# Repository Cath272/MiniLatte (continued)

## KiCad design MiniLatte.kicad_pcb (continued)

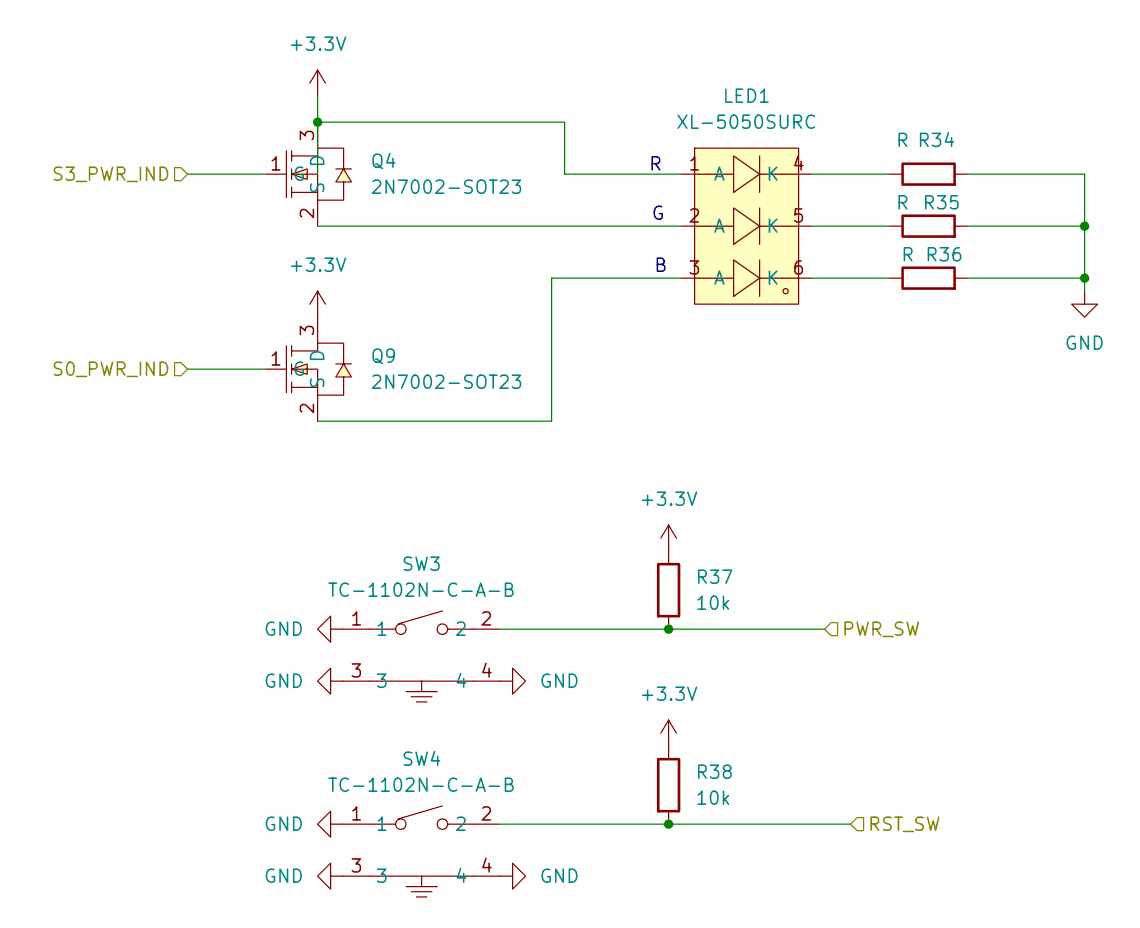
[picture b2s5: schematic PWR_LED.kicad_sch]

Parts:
LED1: XL-5050SURC; LED-ARRAY-SMD_6P-L5.0-W5.0-TL-RD-2; LCSC Part C2843864
Q4, Q9: 2N7002-SOT23; SOT-23_L2.9-W1.3-P1.90-LS2.4-BR; LCSC Part C332103
R34, R35, R36: R; R_0402_1005Metric
R37, R38: 10k; R_0402_1005Metric
SW3, SW4: TC-1102N-C-A-B; SW-TH_TC-1102N-C-A-B; LCSC Part C406152

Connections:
+3.3V: LED1.1 (A), Q4.3 (D), Q9.3 (D), R37.1, R38.1; also elsewhere on the board
/PWR_LED_SW/PWR_SW: R37.2, SW3.2; also elsewhere on the board
/PWR_LED_SW/RST_SW: R38.2, SW4.2; also elsewhere on the board
/PWR_LED_SW/S0_PWR_IND: Q9.1 (G); also elsewhere on the board
/PWR_LED_SW/S3_PWR_IND: Q4.1 (G); also elsewhere on the board
GND: R34.2, R35.2, R36.2, SW3.1, SW3.3, SW3.4, SW4.1, SW4.3, SW4.4; also elsewhere on the board
unnamed: LED1.4 (K), R34.1
unnamed: LED1.5 (K), R35.1
unnamed: LED1.6 (K), R36.1
unnamed: LED1.2 (A), Q4.2 (S)
unnamed: LED1.3 (A), Q9.2 (S)

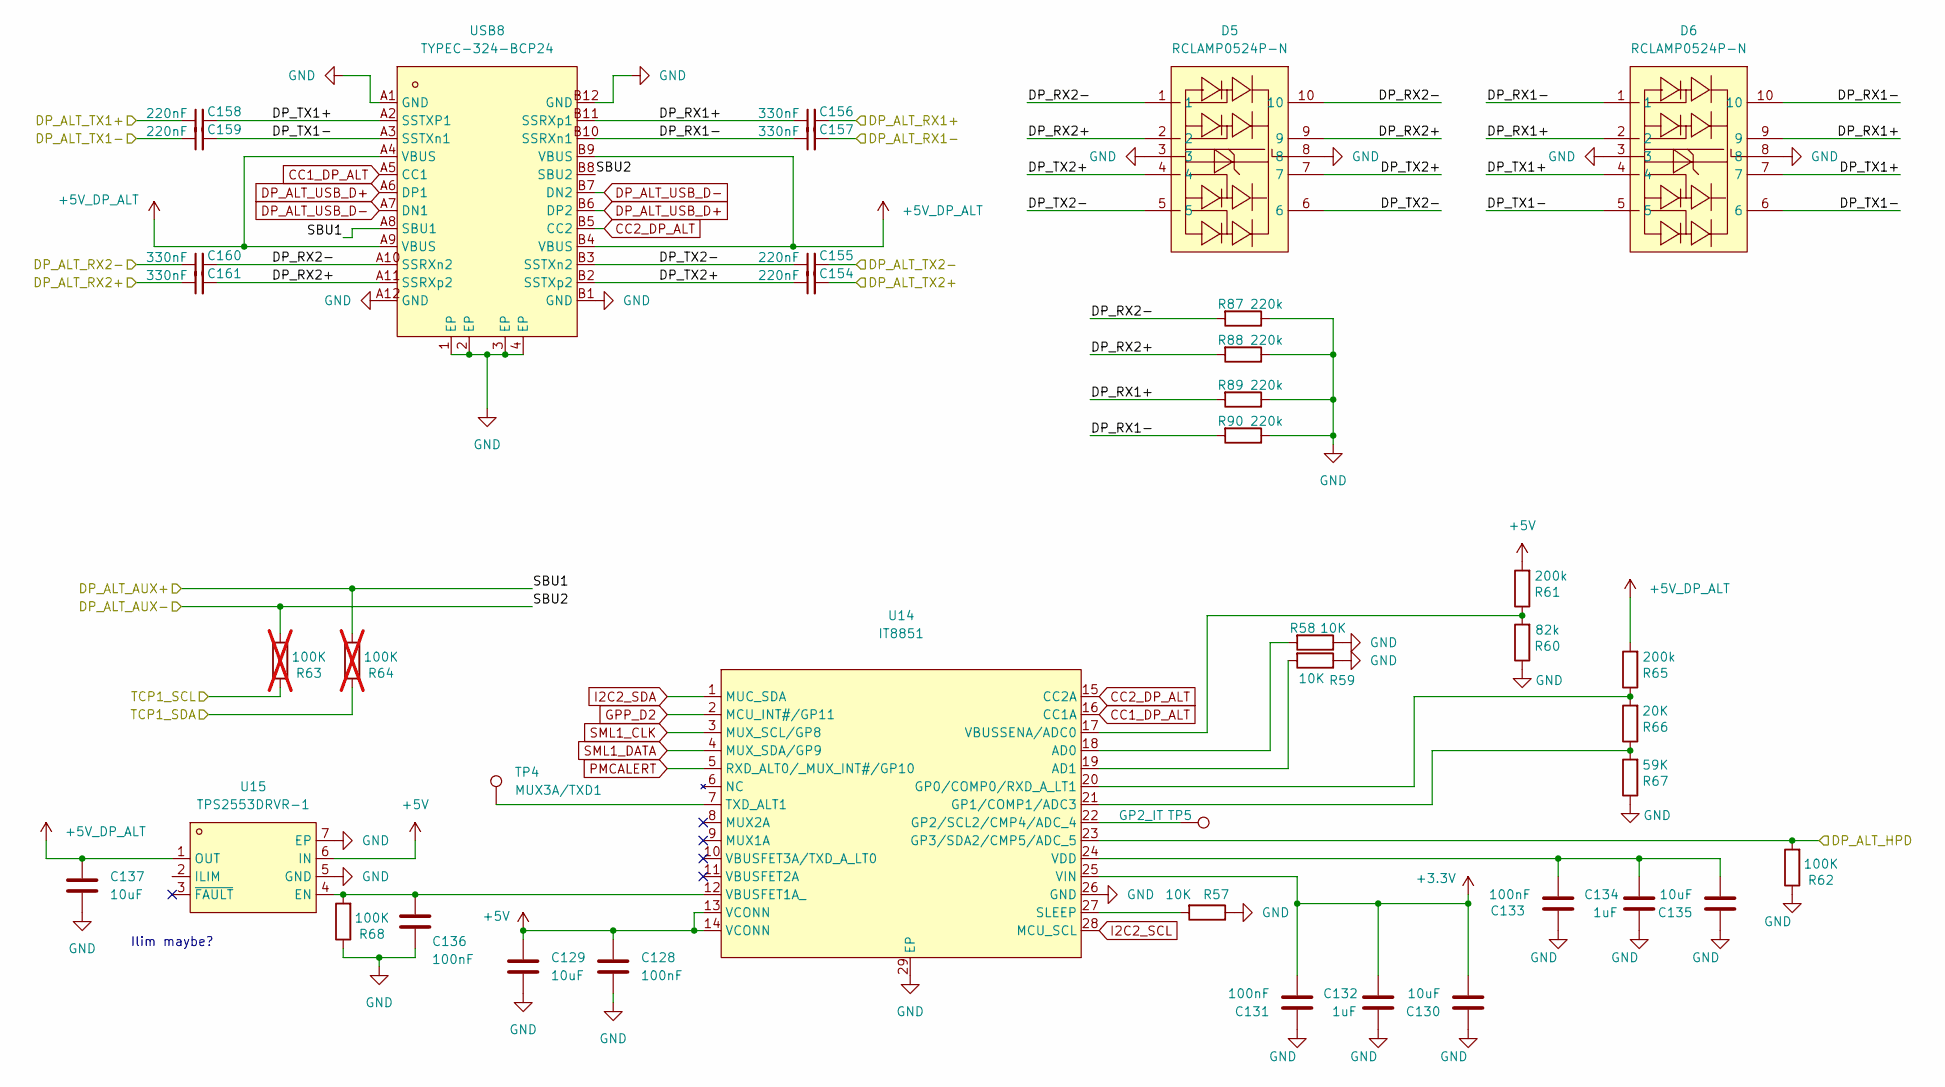
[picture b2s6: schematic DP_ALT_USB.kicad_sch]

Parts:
C128, C131, C133, C136: 100nF; C_0402_1005Metric
C129, C130, C135, C137: 10uF; C_0805_2012Metric
C132, C134: 1uF; C_0603_1608Metric
C154, C155, C158, C159: 220nF; C_0402_1005Metric
C156, C157, C160, C161: 330nF; C_0402_1005Metric
D5, D6: RCLAMP0524P-N; DFN-10L_L2.5-W1.0-P0.50-BL; LCSC Part C316044
R57, R58, R59: 10K; R_0402_1005Metric
R60: 82k; R_0402_1005Metric
R61, R65: 200k; R_0402_1005Metric
R62, R68: 100K; R_0402_1005Metric
R63, R64: 100K; R_0402_1005Metric; not fitted
R66: 20K; R_0402_1005Metric
R67: 59K; R_0402_1005Metric
R87, R88, R89, R90: 220k; R_0402_1005Metric
TP4: MUX3A/TXD1; TestPoint_Pad_D1.0mm
TP5: GP2_IT; TestPoint_Pad_D1.0mm
U14: IT8851; VQFN-28-1EP_4x4mm_P0.45mm_EP2.4x2.4mm
U15: TPS2553DRVR-1; WSON-6_L2.0-W2.0-P0.65-BL-EP; LCSC Part C411878
USB8: TYPEC-324-BCP24; USB-C-SMD_TYPEC-324-BCP24; LCSC Part C2835314

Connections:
+3.3V: C130.2, C131.2, C132.2, U14.25 (VIN); also elsewhere on the board
+5V: C128.1, C129.1, R61.2, U14.13 (VCONN), U14.14 (VCONN), U15.6 (IN); also elsewhere on the board
+5V_DP_ALT: C137.1, R65.2, U15.1 (OUT), USB8.A4 (VBUS), USB8.A9 (VBUS), USB8.B4 (VBUS), USB8.B9 (VBUS)
/DP_ALT_USB/DP_ALT_HPD: R62.2, U14.23 (GP3/SDA2/CMP5/ADC_5); also elsewhere on the board
/DP_ALT_USB/DP_ALT_RX1+: C156.2; also elsewhere on the board
/DP_ALT_USB/DP_ALT_RX1-: C157.2; also elsewhere on the board
/DP_ALT_USB/DP_ALT_RX2+: C161.1; also elsewhere on the board
/DP_ALT_USB/DP_ALT_RX2-: C160.1; also elsewhere on the board
/DP_ALT_USB/DP_ALT_TX1+: C158.1; also elsewhere on the board
/DP_ALT_USB/DP_ALT_TX1-: C159.1; also elsewhere on the board
/DP_ALT_USB/DP_ALT_TX2+: C154.2; also elsewhere on the board
/DP_ALT_USB/DP_ALT_TX2-: C155.2; also elsewhere on the board
/DP_ALT_USB/DP_RX1+: C156.1, D6.2, D6.9, R89.2, USB8.B11 (SSRXp1)
/DP_ALT_USB/DP_RX1-: C157.1, D6.1, D6.10, R90.2, USB8.B10 (SSRXn1)
/DP_ALT_USB/DP_RX2+: C161.2, D5.2, D5.9, R88.2, USB8.A11 (SSRXp2)
/DP_ALT_USB/DP_RX2-: C160.2, D5.1, D5.10, R87.2, USB8.A10 (SSRXn2)
/DP_ALT_USB/DP_TX1+: C158.2, D6.4, D6.7, USB8.A2 (SSTXP1)
/DP_ALT_USB/DP_TX1-: C159.2, D6.5, D6.6, USB8.A3 (SSTXn1)
/DP_ALT_USB/DP_TX2+: C154.1, D5.4, D5.7, USB8.B2 (SSTXp2)
/DP_ALT_USB/DP_TX2-: C155.1, D5.5, D5.6, USB8.B3 (SSTXn2)
/DP_ALT_USB/SBU1: R64.2, USB8.A8 (SBU1); also elsewhere on the board
/DP_ALT_USB/SBU2: R63.2, USB8.B8 (SBU2); also elsewhere on the board
/DP_ALT_USB/TCP1_SCL: R63.1; also elsewhere on the board
/DP_ALT_USB/TCP1_SDA: R64.1; also elsewhere on the board
CC1_DP_ALT: U14.16 (CC1A), USB8.A5 (CC1)
CC2_DP_ALT: U14.15 (CC2A), USB8.B5 (CC2)
DP_ALT_USB_D+: USB8.A6 (DP1), USB8.B6 (DP2); also elsewhere on the board
DP_ALT_USB_D-: USB8.A7 (DN1), USB8.B7 (DN2); also elsewhere on the board
GND: C128.2, C129.2, C130.1, C131.1, C132.1, C133.1, C134.1, C135.1, C136.2, C137.2, D5.3, D5.8, D6.3, D6.8, R57.1, R58.1, R59.1, R60.1, R62.1, R67.1, R68.1, R87.1, R88.1, R89.1, R90.1, U14.26 (GND), U14.29 (EP), U15.5 (GND), U15.7 (EP), USB8.1 (EP), USB8.2 (EP), USB8.3 (EP), USB8.4 (EP), USB8.A1 (GND), USB8.A12 (GND), USB8.B1 (GND), USB8.B12 (GND); also elsewhere on the board
GPP_D2: U14.2 (MCU_INT#/GP11); also elsewhere on the board
I2C2_SCL: U14.28 (MCU_SCL); also elsewhere on the board
I2C2_SDA: U14.1 (MUC_SDA); also elsewhere on the board
unnamed: R58.2, U14.18 (AD0)
unnamed: R59.2, U14.19 (AD1)
unnamed: R65.1, R66.2, U14.20 (GP0/COMP0/RXD_A_LT1)
unnamed: R66.1, R67.2, U14.21 (GP1/COMP1/ADC3)
unnamed: TP5.1, U14.22 (GP2/SCL2/CMP4/ADC_4)
unnamed: R57.2, U14.27 (SLEEP)
unnamed: TP4.1, U14.7 (TXD_ALT1)
unnamed: C136.1, R68.2, U14.12 (VBUSFET1A_), U15.4 (EN)
unnamed: R60.2, R61.1, U14.17 (VBUSSENA/ADC0)
unnamed: C133.2, C134.2, C135.2, U14.24 (VDD)
PMCALERT: U14.5 (RXD_ALT0/_MUX_INT#/GP10); also elsewhere on the board
SML1_CLK: U14.3 (MUX_SCL/GP8); also elsewhere on the board
SML1_DATA: U14.4 (MUX_SDA/GP9); also elsewhere on the board

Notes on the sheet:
Ilim maybe?

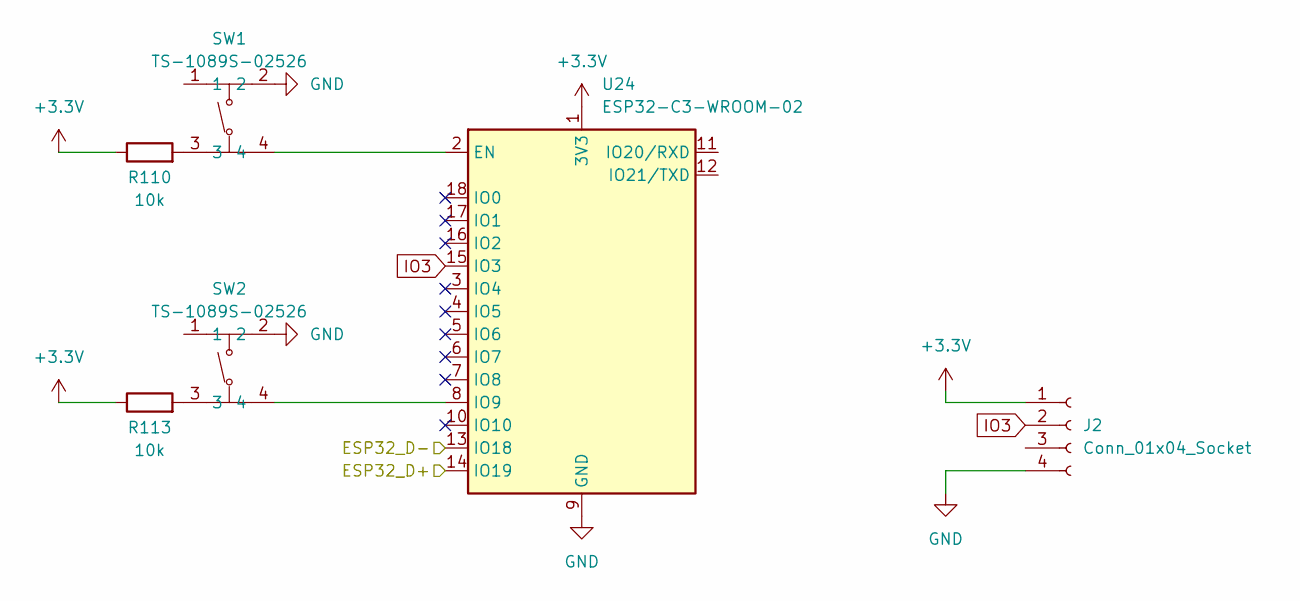
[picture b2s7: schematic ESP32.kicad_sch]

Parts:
J2: Conn_01x04_Socket; PinSocket_1x04_P2.54mm_Vertical
R110, R113: 10k; R_0402_1005Metric
SW1, SW2: TS-1089S-02526; SW-SMD_4P-L4.2-W3.3-P2.15-LS5.1; LCSC Part C455282
U24: ESP32-C3-WROOM-02

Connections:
+3.3V: J2.1, R110.1, R113.1, U24.1 (3V3); also elsewhere on the board
/ESP32/ESP32_D+: U24.14 (IO19); also elsewhere on the board
/ESP32/ESP32_D-: U24.13 (IO18); also elsewhere on the board
GND: J2.4, SW1.2, SW2.2, U24.9 (GND), U24.19 (GND); also elsewhere on the board
IO3: J2.2, U24.15 (IO3)
unnamed: R110.2, SW1.3
unnamed: R113.2, SW2.3
unnamed: SW1.4, U24.2 (EN)
unnamed: SW2.4, U24.8 (IO9)

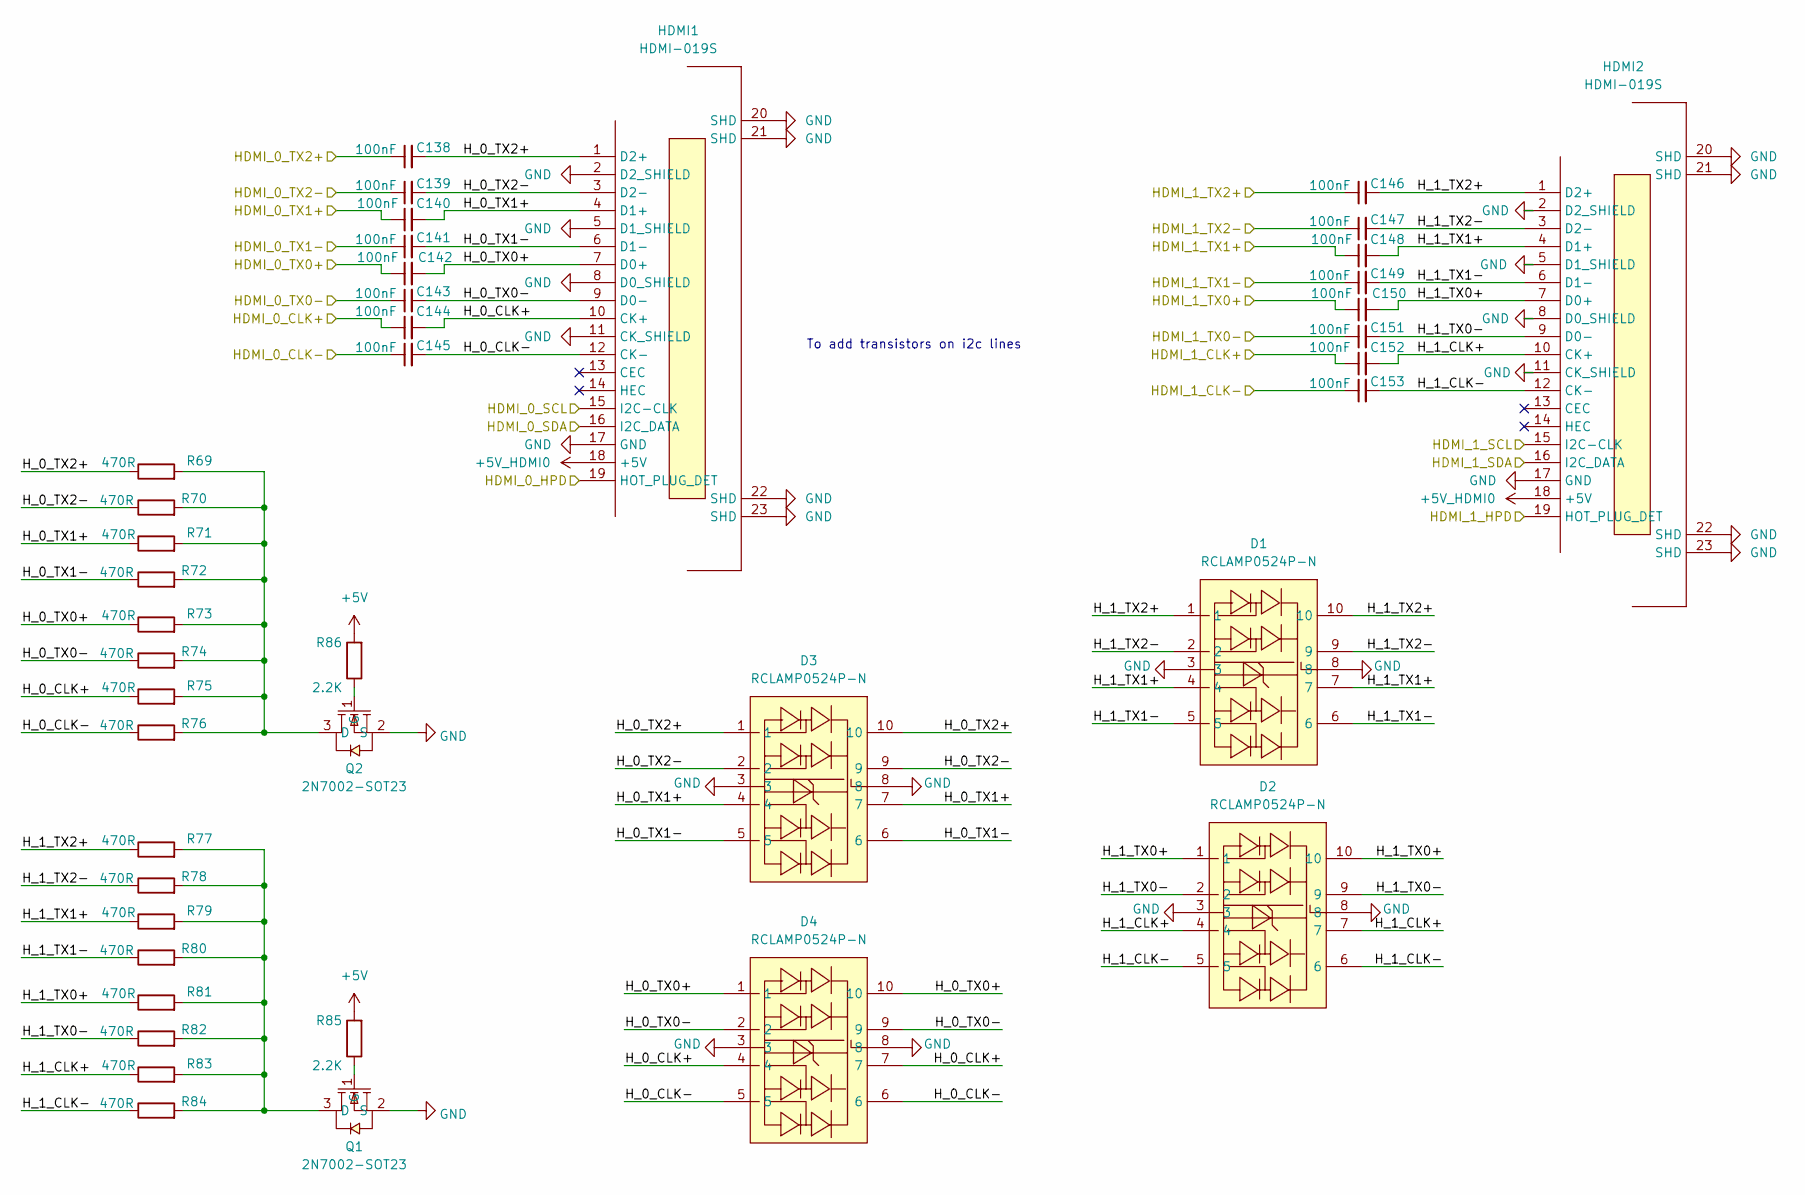
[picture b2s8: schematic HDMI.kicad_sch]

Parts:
C138, C139, C140, C141, C142, C143, C144, C145, C146, C147, C148, C149, C150, C151, C152, C153: 100nF; C_0402_1005Metric
D1, D2, D3, D4: RCLAMP0524P-N; DFN-10L_L2.5-W1.0-P0.50-BL; LCSC Part C316044
HDMI1, HDMI2: HDMI-019S; HDMI-SMD_HDMI-019S; LCSC Part C111617
Q1, Q2: 2N7002-SOT23; SOT-23_L2.9-W1.3-P1.90-LS2.4-BR; LCSC Part C332103
R69, R70, R71, R72, R73, R74, R75, R76, R77, R78, R79, R80, R81, R82, R83, R84: 470R; R_0402_1005Metric
R85, R86: 2.2K; R_0402_1005Metric

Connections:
+5V: R85.2, R86.2; also elsewhere on the board
+5V_HDMI0: HDMI1.18 (+5V), HDMI2.18 (+5V)
/HDMI/HDMI_0_CLK+: C144.1; also elsewhere on the board
/HDMI/HDMI_0_CLK-: C145.1; also elsewhere on the board
/HDMI/HDMI_0_HPD: HDMI1.19 (HOT_PLUG_DET); also elsewhere on the board
/HDMI/HDMI_0_SCL: HDMI1.15 (I2C-CLK); also elsewhere on the board
/HDMI/HDMI_0_SDA: HDMI1.16 (I2C_DATA); also elsewhere on the board
/HDMI/HDMI_0_TX0+: C142.1; also elsewhere on the board
/HDMI/HDMI_0_TX0-: C143.1; also elsewhere on the board
/HDMI/HDMI_0_TX1+: C140.1; also elsewhere on the board
/HDMI/HDMI_0_TX1-: C141.1; also elsewhere on the board
/HDMI/HDMI_0_TX2+: C138.1; also elsewhere on the board
/HDMI/HDMI_0_TX2-: C139.1; also elsewhere on the board
/HDMI/HDMI_1_CLK+: C152.1; also elsewhere on the board
/HDMI/HDMI_1_CLK-: C153.1; also elsewhere on the board
/HDMI/HDMI_1_HPD: HDMI2.19 (HOT_PLUG_DET); also elsewhere on the board
/HDMI/HDMI_1_SCL: HDMI2.15 (I2C-CLK); also elsewhere on the board
/HDMI/HDMI_1_SDA: HDMI2.16 (I2C_DATA); also elsewhere on the board
/HDMI/HDMI_1_TX0+: C150.1; also elsewhere on the board
/HDMI/HDMI_1_TX0-: C151.1; also elsewhere on the board
/HDMI/HDMI_1_TX1+: C148.1; also elsewhere on the board
/HDMI/HDMI_1_TX1-: C149.1; also elsewhere on the board
/HDMI/HDMI_1_TX2+: C146.1; also elsewhere on the board
/HDMI/HDMI_1_TX2-: C147.1; also elsewhere on the board
/HDMI/H_0_CLK+: C144.2, D4.4, D4.7, HDMI1.10 (CK+), R75.1
/HDMI/H_0_CLK-: C145.2, D4.5, D4.6, HDMI1.12 (CK-), R76.1
/HDMI/H_0_TX0+: C142.2, D4.1, D4.10, HDMI1.7 (D0+), R73.1
/HDMI/H_0_TX0-: C143.2, D4.2, D4.9, HDMI1.9 (D0-), R74.1
/HDMI/H_0_TX1+: C140.2, D3.4, D3.7, HDMI1.4 (D1+), R71.1
/HDMI/H_0_TX1-: C141.2, D3.5, D3.6, HDMI1.6 (D1-), R72.1
/HDMI/H_0_TX2+: C138.2, D3.1, D3.10, HDMI1.1 (D2+), R69.1
/HDMI/H_0_TX2-: C139.2, D3.2, D3.9, HDMI1.3 (D2-), R70.1
/HDMI/H_1_CLK+: C152.2, D2.4, D2.7, HDMI2.10 (CK+), R83.1
/HDMI/H_1_CLK-: C153.2, D2.5, D2.6, HDMI2.12 (CK-), R84.1
/HDMI/H_1_TX0+: C150.2, D2.1, D2.10, HDMI2.7 (D0+), R81.1
/HDMI/H_1_TX0-: C151.2, D2.2, D2.9, HDMI2.9 (D0-), R82.1
/HDMI/H_1_TX1+: C148.2, D1.4, D1.7, HDMI2.4 (D1+), R79.1
/HDMI/H_1_TX1-: C149.2, D1.5, D1.6, HDMI2.6 (D1-), R80.1
/HDMI/H_1_TX2+: C146.2, D1.1, D1.10, HDMI2.1 (D2+), R77.1
/HDMI/H_1_TX2-: C147.2, D1.2, D1.9, HDMI2.3 (D2-), R78.1
GND: D1.3, D1.8, D2.3, D2.8, D3.3, D3.8, D4.3, D4.8, HDMI1.2 (D2_SHIELD), HDMI1.5 (D1_SHIELD), HDMI1.8 (D0_SHIELD), HDMI1.11 (CK_SHIELD), HDMI1.17 (GND), HDMI1.20 (SHD), HDMI1.21 (SHD), HDMI1.22 (SHD), HDMI1.23 (SHD), HDMI2.2 (D2_SHIELD), HDMI2.5 (D1_SHIELD), HDMI2.8 (D0_SHIELD), HDMI2.11 (CK_SHIELD), HDMI2.17 (GND), HDMI2.20 (SHD), HDMI2.21 (SHD), HDMI2.22 (SHD), HDMI2.23 (SHD), Q1.2 (S), Q2.2 (S); also elsewhere on the board
unnamed: Q1.3 (D), R77.2, R78.2, R79.2, R80.2, R81.2, R82.2, R83.2, R84.2
unnamed: Q1.1 (G), R85.1
unnamed: Q2.3 (D), R69.2, R70.2, R71.2, R72.2, R73.2, R74.2, R75.2, R76.2
unnamed: Q2.1 (G), R86.1

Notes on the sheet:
To add transistors on i2c lines

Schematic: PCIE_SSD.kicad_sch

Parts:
C71, C72, C73, C74, C75, C76, C77, C78, C79, C80: 220nF; C_0402_1005Metric
CN2, CN3, CN4: APCI0107-P001A; CONN-SMD_APCI0107-P001A; LCSC Part C841661

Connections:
+3.3V: CN2.2, CN2.4, CN2.12, CN2.14, CN2.16, CN2.18, CN2.70, CN2.72, CN2.74, CN3.2, CN3.4, CN3.12, CN3.14, CN3.16, CN3.18, CN3.70, CN3.72, CN3.74, CN4.2, CN4.4, CN4.12, CN4.14, CN4.16, CN4.18, CN4.70, CN4.72, CN4.74; also elsewhere on the board
/PCIE_SSD/PCIE2_L0TX+: C74.1, CN2.49
/PCIE_SSD/PCIE2_L0TX-: C73.1, CN2.47
/PCIE_SSD/PCIE2_L1TX+: C72.1, CN2.37
/PCIE_SSD/PCIE2_L1TX-: C71.1, CN2.35
/PCIE_SSD/PCIE3_L0TX+: C78.1, CN3.49
/PCIE_SSD/PCIE3_L0TX-: C77.1, CN3.47
/PCIE_SSD/PCIE3_L1TX+: C76.1, CN3.37
/PCIE_SSD/PCIE3_L1TX-: C75.1, CN3.35
/PCIE_SSD/PCIE4TX+: C80.1, CN4.49
/PCIE_SSD/PCIE4TX-: C79.1, CN4.47
/PCIE_SSD/PCIE_2_L0_RX+: CN2.43; also elsewhere on the board
/PCIE_SSD/PCIE_2_L0_RX-: CN2.41; also elsewhere on the board
/PCIE_SSD/PCIE_2_L0_TX+: C74.2; also elsewhere on the board
/PCIE_SSD/PCIE_2_L0_TX-: C73.2; also elsewhere on the board
/PCIE_SSD/PCIE_2_L1_RX+: CN2.31; also elsewhere on the board
/PCIE_SSD/PCIE_2_L1_RX-: CN2.29; also elsewhere on the board
/PCIE_SSD/PCIE_2_L1_TX+: C72.2; also elsewhere on the board
/PCIE_SSD/PCIE_2_L1_TX-: C71.2; also elsewhere on the board
/PCIE_SSD/PCIE_3_L0_RX+: CN3.43; also elsewhere on the board
/PCIE_SSD/PCIE_3_L0_RX-: CN3.41; also elsewhere on the board
/PCIE_SSD/PCIE_3_L0_TX+: C78.2; also elsewhere on the board
/PCIE_SSD/PCIE_3_L0_TX-: C77.2; also elsewhere on the board
/PCIE_SSD/PCIE_3_L1_RX+: CN3.31; also elsewhere on the board
/PCIE_SSD/PCIE_3_L1_RX-: CN3.29; also elsewhere on the board
/PCIE_SSD/PCIE_3_L1_TX+: C76.2; also elsewhere on the board
/PCIE_SSD/PCIE_3_L1_TX-: C75.2; also elsewhere on the board
/PCIE_SSD/PCIE_4_RX+: CN4.43; also elsewhere on the board
/PCIE_SSD/PCIE_4_RX-: CN4.41; also elsewhere on the board
/PCIE_SSD/PCIE_4_TX+: C80.2; also elsewhere on the board
/PCIE_SSD/PCIE_4_TX-: C79.2; also elsewhere on the board
GND: CN2.1, CN2.3, CN2.9, CN2.15, CN2.21, CN2.27, CN2.33, CN2.39, CN2.45, CN2.51, CN2.52, CN2.57, CN2.71, CN2.73, CN2.75, CN2.76, CN2.77, CN3.1, CN3.3, CN3.9, CN3.15, CN3.21, CN3.27, CN3.33, CN3.39, CN3.45, CN3.51, CN3.57, CN3.71, CN3.73, CN3.75, CN3.76, CN3.77, CN4.1, CN4.3, CN4.9, CN4.15, CN4.21, CN4.27, CN4.33, CN4.39, CN4.45, CN4.51, CN4.57, CN4.71, CN4.73, CN4.75, CN4.76, CN4.77; also elsewhere on the board
PCIE_2_CLK+: CN2.55; also elsewhere on the board
PCIE_2_CLK-: CN2.53; also elsewhere on the board
PCIE_3_CLK+: CN3.55; also elsewhere on the board
PCIE_3_CLK-: CN3.53; also elsewhere on the board
PCIE_4_CLK+: CN4.55; also elsewhere on the board
PCIE_4_CLK-: CN4.53; also elsewhere on the board
PCIE_CLKREQ3#: CN3.52; also elsewhere on the board
PCIE_CLKREQ4#: CN4.52; also elsewhere on the board
PCIE_RST: CN2.50, CN3.50, CN4.50; also elsewhere on the board
PCIE_WAKE: CN2.54, CN3.54, CN4.54; also elsewhere on the board
SUSCLK_WIFI: CN2.68, CN3.68, CN4.68; also elsewhere on the board

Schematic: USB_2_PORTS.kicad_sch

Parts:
R29: ?k; R_0402_1005Metric
R30, R31: 0R; R_0402_1005Metric
U10: TPS2560DRCR; VSON-10_L3.0-W3.0-P0.50-BL-EP_TPS62410DRCR; LCSC Part C140304
USB5: AF SS-JB17.6; USB-A-TH_AF-SS-JB17.6; LCSC Part C456021

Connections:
+5V: U10.2 (IN), U10.3 (IN); also elsewhere on the board
+5V_USB2_0: U10.9 (OUT1), USB5.1 (VCC)
+5V_USB2_1: U10.8 (OUT2), USB5.5 (VCC)
/USB_2_PORTS/USB2_0+: USB5.3 (D+); also elsewhere on the board
/USB_2_PORTS/USB2_0-: USB5.2 (D-); also elsewhere on the board
/USB_2_PORTS/USB2_1+: USB5.7 (D+); also elsewhere on the board
/USB_2_PORTS/USB2_1-: USB5.6 (D-); also elsewhere on the board
GND: R29.1, R30.2, R31.2, U10.1 (GND), U10.11 (EPAD), USB5.4 (GND), USB5.8 (GND), USB5.9 (SHELL), USB5.10 (SHELL), USB5.11 (SHELL), USB5.12 (SHELL); also elsewhere on the board
unnamed: R30.1, U10.4 (EN1)
unnamed: R31.1, U10.5 (EN2)
unnamed: R29.2, U10.7 (ILIM)
USB_OC#: U10.6 (~FAULT2); also elsewhere on the board

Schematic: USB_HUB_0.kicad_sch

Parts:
C1, C2, C3, C4, C5, C6, C7, C8, C9, C10, C12, C13, C14, C15, C18: 100nF; C_0402_1005Metric
C11, C16: 18pF; C_0402_1005Metric
C17: 10uF; C_0805_2012Metric
R2, R3, R4, R5, R6, R7: 10K; R_0402_1005Metric
R8: 47k; R_0402_1005Metric
R9: 100k; R_0402_1005Metric
R10: 12.4K; R_0402_1005Metric
U1: VL822-QFN76; QFN-76_L9.0-W9.0-P0.40-EP6.3-TL; LCSC Part C2841047
U2: W25Q32JVZPIQ; WSON-8_L6.0-W5.0-P1.27-BL-EP; LCSC Part C571260
Y1: 25Mhz; Crystal_SMD_3225-4Pin_3.2x2.5mm

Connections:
+1.05V: C1.2, C2.2, C3.2, C6.2, C7.2, C8.2, C10.2, C14.2, C15.2, C17.2, C18.1, U1.5 (VCC10I), U1.8 (VCC10I), U1.11 (VDD), U1.14 (VCC10I), U1.27 (VCC10I), U1.30 (VDD), U1.33 (VCC10I), U1.36 (VCC10I), U1.48 (VDD), U1.51 (VCC10I), U1.54 (VCC10I), U1.67 (VDD); also elsewhere on the board
+3.3V: C4.2, C5.2, C9.2, C12.2, C13.2, R2.1, R3.1, R5.1, R6.1, R7.2, R8.2, U1.17 (VCC33I), U1.24 (VCC33I), U1.46 (VCC33I), U1.62 (VCC33I), U1.73 (VCC33I), U2.3 (/WP(IO2)), U2.7 (/HOLDor/RESET(IO3)), U2.8 (VCC); also elsewhere on the board
/USB_3/SS_HUB_0_RX+: U1.53 (SSRX0+); also elsewhere on the board
/USB_3/SS_HUB_0_RX-: U1.52 (SSRX0–); also elsewhere on the board
/USB_3/SS_HUB_0_TX+: U1.50 (SSTX0+); also elsewhere on the board
/USB_3/SS_HUB_0_TX-: U1.49 (SSTX0–); also elsewhere on the board
/USB_3/USB_HUB_0/GL3224/DFP1_D+: U1.9 (HSD1+); also elsewhere on the board
/USB_3/USB_HUB_0/GL3224/DFP1_D-: U1.10 (HSD1–); also elsewhere on the board
/USB_3/USB_HUB_0/GL3224/DFP1_RX+: U1.6 (SSRX1+); also elsewhere on the board
/USB_3/USB_HUB_0/GL3224/DFP1_RX-: U1.7 (SSRX1–); also elsewhere on the board
/USB_3/USB_HUB_0/GL3224/DFP1_TX+: U1.3 (SSTX1+); also elsewhere on the board
/USB_3/USB_HUB_0/GL3224/DFP1_TX-: U1.4 (SSTX1–); also elsewhere on the board
/USB_3/USB_HUB_0/HUB_0_PORTS/DFP2_D+: U1.18 (HSD2+); also elsewhere on the board
/USB_3/USB_HUB_0/HUB_0_PORTS/DFP2_D-: U1.19 (HSD2–); also elsewhere on the board
/USB_3/USB_HUB_0/HUB_0_PORTS/DFP2_RX+: U1.15 (SSRX2+); also elsewhere on the board
/USB_3/USB_HUB_0/HUB_0_PORTS/DFP2_RX-: U1.16 (SSRX2–); also elsewhere on the board
/USB_3/USB_HUB_0/HUB_0_PORTS/DFP2_TX+: U1.12 (SSTX2+); also elsewhere on the board
/USB_3/USB_HUB_0/HUB_0_PORTS/DFP2_TX-: U1.13 (SSTX2–); also elsewhere on the board
/USB_3/USB_HUB_0/HUB_0_PORTS/DFP3_D+: U1.22 (HSD3+); also elsewhere on the board
/USB_3/USB_HUB_0/HUB_0_PORTS/DFP3_D-: U1.23 (HSD3–); also elsewhere on the board
/USB_3/USB_HUB_0/HUB_0_PORTS/DFP3_RX+: U1.28 (SSRX3+); also elsewhere on the board
/USB_3/USB_HUB_0/HUB_0_PORTS/DFP3_RX-: U1.29 (SSRX3–); also elsewhere on the board
/USB_3/USB_HUB_0/HUB_0_PORTS/DFP3_TX+: U1.25 (SSTX3+); also elsewhere on the board
/USB_3/USB_HUB_0/HUB_0_PORTS/DFP3_TX-: U1.26 (SSTX3–); also elsewhere on the board
/USB_3/USB_HUB_0/HUB_0_PORTS/DFP4_D+: U1.37 (HSD4+); also elsewhere on the board
/USB_3/USB_HUB_0/HUB_0_PORTS/DFP4_D-: U1.38 (HSD4–); also elsewhere on the board
/USB_3/USB_HUB_0/HUB_0_PORTS/DFP4_RX+: U1.34 (SSRX4+); also elsewhere on the board
/USB_3/USB_HUB_0/HUB_0_PORTS/DFP4_RX-: U1.35 (SSRX4–); also elsewhere on the board
/USB_3/USB_HUB_0/HUB_0_PORTS/DFP4_TX+: U1.31 (SSTX4+); also elsewhere on the board
/USB_3/USB_HUB_0/HUB_0_PORTS/DFP4_TX-: U1.32 (SSTX4–); also elsewhere on the board
GND: C1.1, C2.1, C3.1, C4.1, C5.1, C6.1, C7.1, C8.1, C9.1, C10.1, C11.2, C12.1, C13.1, C14.1, C15.1, C16.2, C17.1, C18.2, R4.2, R9.1, R10.1, U1.77 (EP), U2.4 (GND), U2.9 (EP), Y1.2, Y1.4; also elsewhere on the board
H0_USBOC2: U1.75 (USBOC2); also elsewhere on the board
H0_USBOC3: U1.20 (USBOC3); also elsewhere on the board
H0_USBOC4: U1.40 (USBOC4)
H0_USBPE2: U1.76 (USBPE2); also elsewhere on the board
H0_USBPE3: U1.21 (USBPE3); also elsewhere on the board
H0_USBPE4: U1.39 (USBPE4)
unnamed: R5.2, U1.65 (GPIO7/SMDAT)
unnamed: R6.2, U1.66 (GPIO8/SMCLK)
unnamed: R10.2, U1.47 (REXT)
unnamed: R4.1, U1.74 (TESTEN)
unnamed: C16.1, U1.45 (USB3XI), Y1.3
unnamed: C11.1, U1.44 (USB3XO), Y1.1
unnamed: U1.69 (USBLED1/SPISI), U2.5 (DI(IO0))
unnamed: U1.70 (USBLED2/SPICK), U2.6 (CLK)
unnamed: U1.71 (USBLED3/SPISO), U2.2 (DO(IO1))
unnamed: U1.72 (USBLED4/SPICS), U2.1 (/CS)
unnamed: R3.2, U1.41 (USBOC0)
unnamed: R2.2, U1.1 (USBOC1)
unnamed: R8.1, R9.2, U1.43 (VBUSDET0)
unnamed: R7.1, U1.68 (~RESET)
USB2_P1+: U1.55 (HSD0+); also elsewhere on the board
USB2_P1-: U1.56 (HSD0–); also elsewhere on the board

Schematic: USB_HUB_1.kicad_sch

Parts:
C102, C103, C104, C105, C106, C107, C108, C109, C110, C111, C113, C114, C115, C116, C119: 100nF; C_0402_1005Metric
C112, C117: 18pF; C_0402_1005Metric
C118: 10uF; C_0805_2012Metric
R45, R46, R47, R48, R49, R50: 10K; R_0402_1005Metric
R51: 47k; R_0402_1005Metric
R52: 100k; R_0402_1005Metric
R53: 12.4K; R_0402_1005Metric
U11: VL822-QFN76; QFN-76_L9.0-W9.0-P0.40-EP6.3-TL; LCSC Part C2841047
U12: W25Q32JVZPIQ; WSON-8_L6.0-W5.0-P1.27-BL-EP; LCSC Part C571260
Y4: 25Mhz; Crystal_SMD_3225-4Pin_3.2x2.5mm

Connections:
+1.05V: C102.2, C103.2, C104.2, C107.2, C108.2, C109.2, C111.2, C115.2, C116.2, C118.2, C119.1, U11.5 (VCC10I), U11.8 (VCC10I), U11.11 (VDD), U11.14 (VCC10I), U11.27 (VCC10I), U11.30 (VDD), U11.33 (VCC10I), U11.36 (VCC10I), U11.48 (VDD), U11.51 (VCC10I), U11.54 (VCC10I), U11.67 (VDD); also elsewhere on the board
+3.3V: C105.2, C106.2, C110.2, C113.2, C114.2, R45.1, R46.1, R48.1, R49.1, R50.2, R51.2, U11.17 (VCC33I), U11.24 (VCC33I), U11.46 (VCC33I), U11.62 (VCC33I), U11.73 (VCC33I), U12.3 (/WP(IO2)), U12.7 (/HOLDor/RESET(IO3)), U12.8 (VCC); also elsewhere on the board
/USB_3/SS_HUB_1_RX+: U11.53 (SSRX0+); also elsewhere on the board
/USB_3/SS_HUB_1_RX-: U11.52 (SSRX0–); also elsewhere on the board
/USB_3/SS_HUB_1_TX+: U11.50 (SSTX0+); also elsewhere on the board
/USB_3/SS_HUB_1_TX-: U11.49 (SSTX0–); also elsewhere on the board
/USB_3/USB_HUB_1/HUB_1_PORTS/DFP1_D+: U11.9 (HSD1+); also elsewhere on the board
/USB_3/USB_HUB_1/HUB_1_PORTS/DFP1_D-: U11.10 (HSD1–); also elsewhere on the board
/USB_3/USB_HUB_1/HUB_1_PORTS/DFP1_RX+: U11.6 (SSRX1+); also elsewhere on the board
/USB_3/USB_HUB_1/HUB_1_PORTS/DFP1_RX-: U11.7 (SSRX1–); also elsewhere on the board
/USB_3/USB_HUB_1/HUB_1_PORTS/DFP1_TX+: U11.3 (SSTX1+); also elsewhere on the board
/USB_3/USB_HUB_1/HUB_1_PORTS/DFP1_TX-: U11.4 (SSTX1–); also elsewhere on the board
/USB_3/USB_HUB_1/HUB_1_PORTS/DFP2_D+: U11.18 (HSD2+); also elsewhere on the board
/USB_3/USB_HUB_1/HUB_1_PORTS/DFP2_D-: U11.19 (HSD2–); also elsewhere on the board
/USB_3/USB_HUB_1/HUB_1_PORTS/DFP2_RX+: U11.15 (SSRX2+); also elsewhere on the board
/USB_3/USB_HUB_1/HUB_1_PORTS/DFP2_RX-: U11.16 (SSRX2–); also elsewhere on the board
/USB_3/USB_HUB_1/HUB_1_PORTS/DFP2_TX+: U11.12 (SSTX2+); also elsewhere on the board
/USB_3/USB_HUB_1/HUB_1_PORTS/DFP2_TX-: U11.13 (SSTX2–); also elsewhere on the board
/USB_3/USB_HUB_1/HUB_1_PORTS/DFP3_D+: U11.22 (HSD3+); also elsewhere on the board
/USB_3/USB_HUB_1/HUB_1_PORTS/DFP3_D-: U11.23 (HSD3–); also elsewhere on the board
/USB_3/USB_HUB_1/HUB_1_PORTS/DFP3_RX+: U11.28 (SSRX3+); also elsewhere on the board
/USB_3/USB_HUB_1/HUB_1_PORTS/DFP3_RX-: U11.29 (SSRX3–); also elsewhere on the board
/USB_3/USB_HUB_1/HUB_1_PORTS/DFP3_TX+: U11.25 (SSTX3+); also elsewhere on the board
/USB_3/USB_HUB_1/HUB_1_PORTS/DFP3_TX-: U11.26 (SSTX3–); also elsewhere on the board
/USB_3/USB_HUB_1/HUB_1_PORTS/DFP4_D+: U11.37 (HSD4+); also elsewhere on the board
/USB_3/USB_HUB_1/HUB_1_PORTS/DFP4_D-: U11.38 (HSD4–); also elsewhere on the board
/USB_3/USB_HUB_1/HUB_1_PORTS/DFP4_RX+: U11.34 (SSRX4+); also elsewhere on the board
/USB_3/USB_HUB_1/HUB_1_PORTS/DFP4_RX-: U11.35 (SSRX4–); also elsewhere on the board
/USB_3/USB_HUB_1/HUB_1_PORTS/DFP4_TX+: U11.31 (SSTX4+); also elsewhere on the board
/USB_3/USB_HUB_1/HUB_1_PORTS/DFP4_TX-: U11.32 (SSTX4–); also elsewhere on the board
GND: C102.1, C103.1, C104.1, C105.1, C106.1, C107.1, C108.1, C109.1, C110.1, C111.1, C112.2, C113.1, C114.1, C115.1, C116.1, C117.2, C118.1, C119.2, R47.2, R52.1, R53.1, U11.77 (EP), U12.4 (GND), U12.9 (EP), Y4.2, Y4.4; also elsewhere on the board
H1_USBOC2: U11.75 (USBOC2); also elsewhere on the board
H1_USBOC3: U11.20 (USBOC3); also elsewhere on the board
H1_USBOC4: U11.40 (USBOC4); also elsewhere on the board
H1_USBPE2: U11.76 (USBPE2); also elsewhere on the board
H1_USBPE3: U11.21 (USBPE3); also elsewhere on the board
H1_USBPE4: U11.39 (USBPE4); also elsewhere on the board
unnamed: R48.2, U11.65 (GPIO7/SMDAT)
unnamed: R49.2, U11.66 (GPIO8/SMCLK)
unnamed: R53.2, U11.47 (REXT)
unnamed: R47.1, U11.74 (TESTEN)
unnamed: C117.1, U11.45 (USB3XI), Y4.3
unnamed: C112.1, U11.44 (USB3XO), Y4.1
unnamed: U11.69 (USBLED1/SPISI), U12.5 (DI(IO0))
unnamed: U11.70 (USBLED2/SPICK), U12.6 (CLK)
unnamed: U11.71 (USBLED3/SPISO), U12.2 (DO(IO1))
unnamed: U11.72 (USBLED4/SPICS), U12.1 (/CS)
unnamed: R46.2, U11.41 (USBOC0)
unnamed: R45.2, U11.1 (USBOC1)
unnamed: R51.1, R52.2, U11.43 (VBUSDET0)
unnamed: R50.1, U11.68 (~RESET)
USB2_P2+: U11.55 (HSD0+); also elsewhere on the board
USB2_P2-: U11.56 (HSD0–); also elsewhere on the board

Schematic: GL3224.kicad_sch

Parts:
C27, C28, C31, C32, C33, C37, C38, C39, C40, C81, C82, C83, C84: 100nF; C_0402_1005Metric
C29, C30: 18pF; C_0402_1005Metric
C34: 22uF; C_0805_2012Metric
C35, C36: 10uF; C_0805_2012Metric
Card1: SD-006M; SD-SMD_SD-006M; LCSC Part C125615
Card2: TF-01A; TF-SMD_TF-01A; LCSC Part C91145
R14: 680R; R_0402_1005Metric
U4: GL3224-ONY04; QFN-48_L7.0-W7.0-P0.50-BL-EP5.1; LCSC Part C157358
U5: W25Q32JVZPIQ; WSON-8_L6.0-W5.0-P1.27-BL-EP; LCSC Part C571260
Y2: 25Mhz; Crystal_SMD_3225-4Pin_3.2x2.5mm

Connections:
+3.3V: U5.3 (/WP(IO2)), U5.7 (/HOLDor/RESET(IO3)), U5.8 (VCC); also elsewhere on the board
+5V: C34.1, U4.22 (VBUS); also elsewhere on the board
/USB_3/USB_HUB_0/GL3224/DFP1_D+: U4.5 (DP); also elsewhere on the board
/USB_3/USB_HUB_0/GL3224/DFP1_D-: U4.4 (DM); also elsewhere on the board
/USB_3/USB_HUB_0/GL3224/DFP1_DRX+: C82.1, U4.8 (TXP)
/USB_3/USB_HUB_0/GL3224/DFP1_DRX-: C81.2, U4.7 (TXN)
/USB_3/USB_HUB_0/GL3224/DFP1_DTX+: C84.1, U4.11 (RXP)
/USB_3/USB_HUB_0/GL3224/DFP1_DTX-: C83.2, U4.10 (RXN)
/USB_3/USB_HUB_0/GL3224/DFP1_RX+: C82.2; also elsewhere on the board
/USB_3/USB_HUB_0/GL3224/DFP1_RX-: C81.1; also elsewhere on the board
/USB_3/USB_HUB_0/GL3224/DFP1_TX+: C84.2; also elsewhere on the board
/USB_3/USB_HUB_0/GL3224/DFP1_TX-: C83.1; also elsewhere on the board
GL_CLK: U4.19 (SPI_CK), U5.6 (CLK)
GL_CS: U4.20 (SPI_CS), U5.1 (/CS)
GL_MISO: U4.17 (SPI_MISO), U5.2 (DO(IO1))
GL_MOSI: U4.18 (SPI_MOSI), U5.5 (DI(IO0))
GND: C27.1, C28.2, C29.2, C30.2, C31.2, C32.2, C33.1, C34.2, C35.2, C36.2, C37.2, C38.1, C39.2, C40.1, Card1.3 (Vss1), Card1.6 (Vss2), Card1.12, Card1.13, Card2.6 (VSS), Card2.10 (GND), Card2.11 (GND), Card2.12 (GND), Card2.13 (GND), R14.2, U4.3 (GND), U4.12 (GND), U4.35 (MS2_INS/SD2_WP), U4.49 (EP), U5.4 (GND), U5.9 (EP), Y2.2, Y2.4; also elsewhere on the board
unnamed: C27.2, U4.6 (AVDD33)
unnamed: C31.1, U4.15 (AVDD33)
unnamed: C32.1, U4.44 (DVDD33)
unnamed: C37.1, U4.34 (DVDD33)
unnamed: C40.2, U4.25 (DVDD33)
unnamed: C28.1, U4.9 (AVDD12)
unnamed: C39.1, U4.26 (DVDD12)
unnamed: R14.1, U4.16 (RTERM)
unnamed: C33.2, U4.43 (VUHS_1)
unnamed: C38.2, U4.33 (VUHS_2)
unnamed: C29.1, U4.13 (X1), Y2.1
unnamed: C30.1, U4.14 (X2), Y2.3
S1CDZ: Card1.CD, U4.1 (SD1_CDZ)
S1CLK: Card1.5 (CLK), U4.39 (S1CK_M1D0)
S1CMD: Card1.2 (CMD), U4.40 (S1CM_M1D2)
S1D0: Card1.7 (DAT0), U4.38 (S1D0_M1D1)
S1D1: Card1.8 (DAT1), U4.37 (S1D1_M1BS)
S1D2: Card1.9 (DAT2), U4.42 (S1D2_M1CK)
S1D3: Card1.1 (CD/DAT3), U4.41 (S1D3_M1D3)
S1_VCC: C35.1, Card1.4 (VDD), U4.23 (S1M1_VCC)
S1_WP: Card1.WP, U4.2 (MS1_INS/SD1_WP)
S2CDZ: Card2.9 (CD), U4.36 (SD2_CDZ)
S2CLK: Card2.5 (CLK(SCLK)), U4.29 (S2CK_M2D0)
S2CMD: Card2.3 (CMD(DI)), U4.30 (S2CM_M2D2)
S2D0: Card2.7 (DAT0(D0)), U4.28 (S2D0_M2D1)
S2D1: Card2.8 (DAT1(RSV)), U4.27 (S2D1_M2BS)
S2D2: Card2.1 (DAT2(RSV)), U4.32 (S2D2_M2CK)
S2D3: Card2.2 (CDDAT3(CS)), U4.31 (S2D3_M2D3)
S2_VCC: C36.1, Card2.4 (VDD), U4.24 (S2M2_VCC)
